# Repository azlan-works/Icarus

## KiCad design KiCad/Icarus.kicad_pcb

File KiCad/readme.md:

These files are exports from EasyEda and may not be 100% accurate

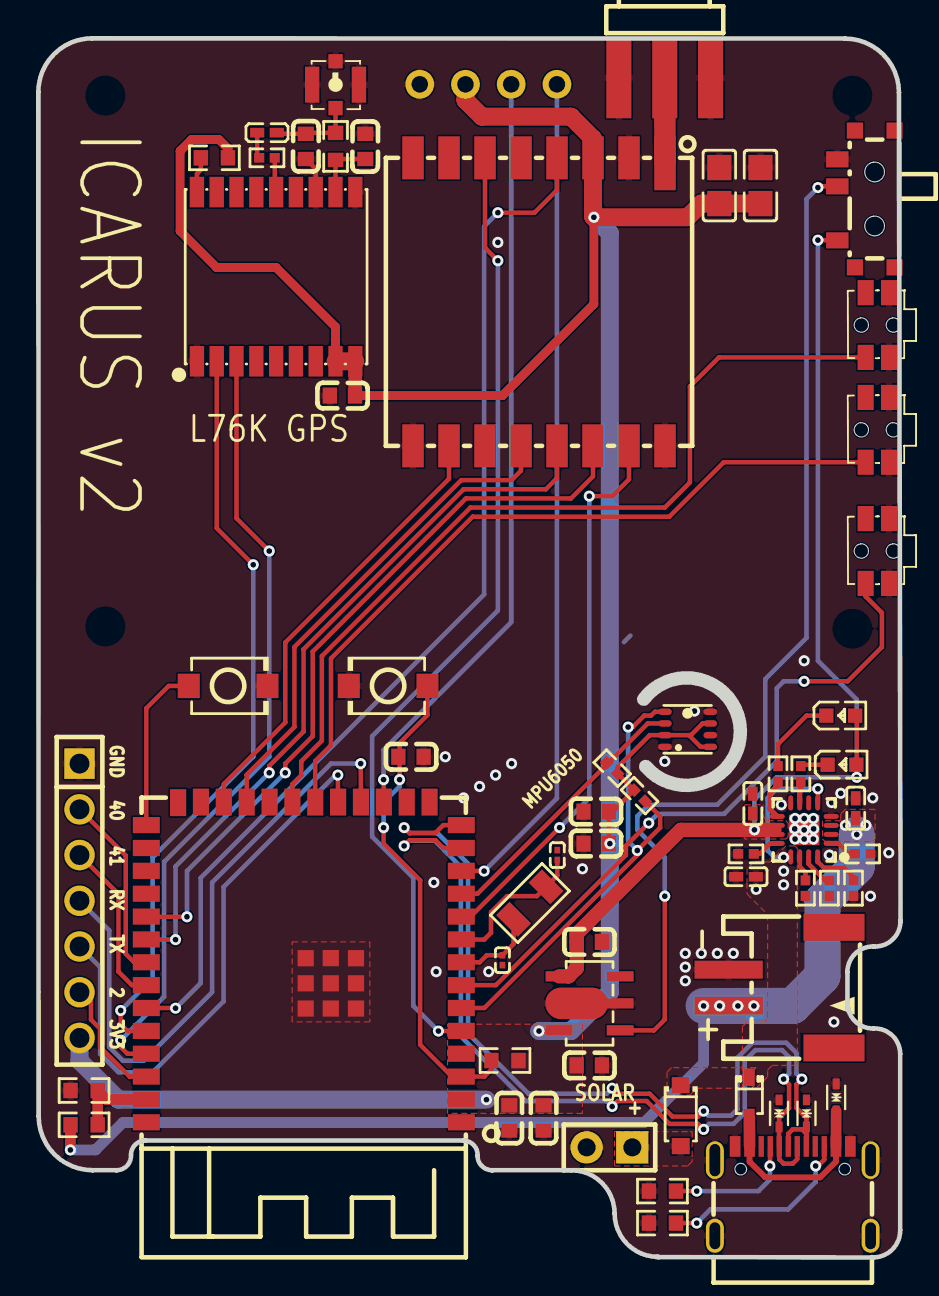
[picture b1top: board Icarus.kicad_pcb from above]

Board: 2 copper layers, 47.9 x 67.7 mm, 63 parts (1 on the bottom side), 53 nets.

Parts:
BME280: LGA-8_BME280_BL
BOOT: SW-SMD_L3.9-W3.0-P4.45
C1, C2: C0805
C4, C5, C6, C7, C8, C10, C11, C12, C13, C17: C0603
C15, C16: C0201
C18, C19, C20: C0402
CHG1: LED0603-RD
CN1: CONN-SMD_P2.00_S2B-PH-SM4-TB-LF-SN
D2: SOD-123_L2.6-W1.7-LS3.5-RD
D3: SOD-323_L1.7-W1.3-LS2.5-RD-1
DOWN: KEY-SMD_4P-SKSCLXX010
GOOD1: LED0603-RD
L2: L0402
P1: 2.54MM4PIN
R1, R2, R6, R7, R8, R23, R24: R0603
R3, R4, R5, R9, R10, R11, R12, R13, R14, R22: R0402
RA-01SH: WIRELM-SMD_RA-01SH
RESET: SW-SMD_L3.9-W3.0-P4.45
SELECT: KEY-SMD_4P-SKSCLXX010
SOLAR: HDR-TH_2P-P2.54-V-M-1
SW1: SW-SMD_SK-3296S-01-L2
U1: WIRELM-SMD_ESP32-S3-WROOM-1
U2: OSC-SMD_L3.2-W1.5
U3: SOT-89-5_L4.5-W2.5-P1.50-LS4.4-BR
U4, U5, U6: SOD-523_L1.2-W0.8-LS1.6-BI
U7: HDR-TH_7P-P2.54-V-M
U10: SMA-SMD_SMA-KHD9
U11: QFN-16_L3.0-W3.0-P0.50-TL-EP1.7
U16: GPSM-SMD_18P-L10.1-W9.7-P1.10
U17: IPEX-SMD_4P-L2.6-W2.6-LS3.0
U18: CERT-SMALL-SILK
UP: KEY-SMD_4P-SKSCLXX010
USB-C: USB-C-SMD_TYPEC-304J-BCP16

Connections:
+3V3: BME280.2, BME280.6, BME280.8, C1.2, C2.2, C5.2, C6.2, C7.2, C11.2, C12.2, C13.1, P1.2, R1.2, R11.2, R12.2, R24.2, RA-01SH.3, U1.2, U3.5, U7.7, U16.8, U16.9
+5V: C18.2, D2.1, D3.1, U11.5, U11.13
BME-SCK: BME280.4, R11.1, U1.6
BME-SDA: BME280.3, R12.1, U1.11
BUSY: RA-01SH.10, U1.24
C10_1: C10.1, R23.1, U16.11
CHG1_1: CHG1.1, R3.2
D+: U1.14, U5.1, USB-C.A6, USB-C.B6
D-: U1.13, U6.1, USB-C.A7, USB-C.B7
DIO1: RA-01SH.6, U1.5
EN: C8.2, R1.1, RESET.1, U1.3
GND: BME280.1, BME280.5, BME280.7, BOOT.2, C1.1, C2.1, C4.1, C5.1, C6.1, C7.1, C8.1, C10.2, C11.1, C12.1, C13.2, C15.1, C16.1, C17.2, C18.1, C19.1, C20.1, CN1.2, DOWN.1, DOWN.2, P1.1, R5.2, R6.2, R7.2, R8.1, R9.1, R10.1, R13.1, R14.2, RA-01SH.2, RA-01SH.9, RA-01SH.16, RESET.2, SELECT.1, SELECT.2, SOLAR.2, SW1.3, U1.1, U1.40, U1.41, U3.2, U4.2, U5.2, U6.2, U7.1, U10.1, U10.3, U10.4, U10.5, U11.4, U11.6, U11.8, U11.17, U16.1, U16.10, U16.12, U17.1, U17.3, U17.4, UP.1, UP.2, USB-C.13, USB-C.14, USB-C.15, USB-C.16, USB-C.A1B12, USB-C.B1A12
GOOD1_1: GOOD1.1, R4.2
GPIO0: BOOT.1, U1.27
GPIO2: U1.38, U7.6
GPIO7: SELECT.3, U1.7
GPIO8: P1.4, U1.12
GPIO9: P1.3, U1.17
GPIO10: U1.18, U7.4
GPIO11: U1.19, U7.5
GPIO12: DOWN.3, U1.20
GPIO13: U1.21, UP.3
GPIO15: C16.2, U1.8, U2.2
GPIO16: C15.2, U1.9, U2.1
GPIO40: U1.33, U7.2
GPIO41: U1.34, U7.3
L2_1: L2.1, R22.2
MISO: RA-01SH.13, U1.32
MOSI: RA-01SH.14, U1.31
NSS: RA-01SH.15, U1.10
R22_1: R22.1, U16.14
R24_1: R24.1, U16.18
RA-01SH_1: RA-01SH.1, U10.2
RESET: RA-01SH.4, U1.35
RXD0: U1.36, U16.2
SCK: RA-01SH.12, U1.23
SOLAR_1: D2.2, SOLAR.1
TXD0: U1.37, U16.3
U1_39: R2.1, R8.2, U1.39
U3_1: SW1.2, U3.1
U11_1: R5.1, U11.1
U11_7: R4.1, U11.7
U11_9: R3.1, U11.9
U11_12: R13.2, U11.12
U11_14: R14.1, U11.14
U11_15: R10.2, U11.15
U11_16: R9.2, U11.16
U17_2: C17.1, L2.2, R23.2, U17.2
USB-C_A5: R6.1, USB-C.A5
USB-C_B5: R7.1, USB-C.B5
VBAT+: C20.2, CN1.1, R2.2, U11.2, U11.3
VIN: D3.2, U4.1, USB-C.A4B9, USB-C.B4A9
VSYS: C4.2, C19.2, CHG1.2, GOOD1.2, SW1.1, U3.4, U11.10, U11.11
